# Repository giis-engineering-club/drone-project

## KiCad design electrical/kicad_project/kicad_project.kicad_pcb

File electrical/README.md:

# Electrical Engineering Subsystem (Flight Controller PCBA)

## Motivation
To design a highly robust, EMI-shielded 4-layer Power Distribution Network (PDN) and microcontroller logic board. This board must survive the extreme $di/dt$ inductive spikes generated by 40A ESC switching while providing mathematically clean SPI data to the ESP32 for 1000Hz PID loop execution.

## Architecture (Hierarchical Sheets)
We will use a Top-Down Hierarchical design in KiCad to keep the schematic industry-grade.
1. **`top_level.sch`**: The master block diagram connecting the sub-sheets.
2. **`power_distribution.sch`**: 5V to 3.3V LDO Regulator, LC filtering, and bulk/decoupling capacitors.
3. **`mcu_esp32.sch`**: The ESP32 logic, strapping pins, and UART/Programming headers.
4. **`sensors_imu.sch`**: The BMI270/MPU6000 IMU, SPI bus wiring, and strict decoupling.
5. **`io_connectors.sch`**: The ESC DSHOT pads, battery voltage sensing voltage-divider, and ESP-NOW RX pins.

## Critical Formulations
- **LC Filter Resonance (For IMU Power Cleanliness):** 
  $f_{res} = \frac{1}{2\pi \sqrt{L C}}$
  We must ensure $f_{res}$ is well below the 24kHz PWM frequency of the ESC to block high-frequency noise.
- **Trace Width Ampacity (IPC-2221):**
  $I = k \cdot \Delta T^b \cdot A^c$ 
  5V traces must handle 1A. Signal traces handle mere mA.
- **EMI Loop Area Minimization:**
  $V_{noise} = - \frac{d}{dt} \int \mathbf{B} \cdot d\mathbf{A}$
  Solid GND plane placed exactly 0.1mm below Layer 1 signal traces ensures $d\mathbf{A} \to 0$.

## Stack & Standards
- **EDA:** KiCad 8.0 (Apple Silicon Native)
- **Simulation:** NGSpice (Transient Power Analysis)
- **Manufacturing:** JLCPCB (4-Layer, 1oz Copper, SMT Assembly)

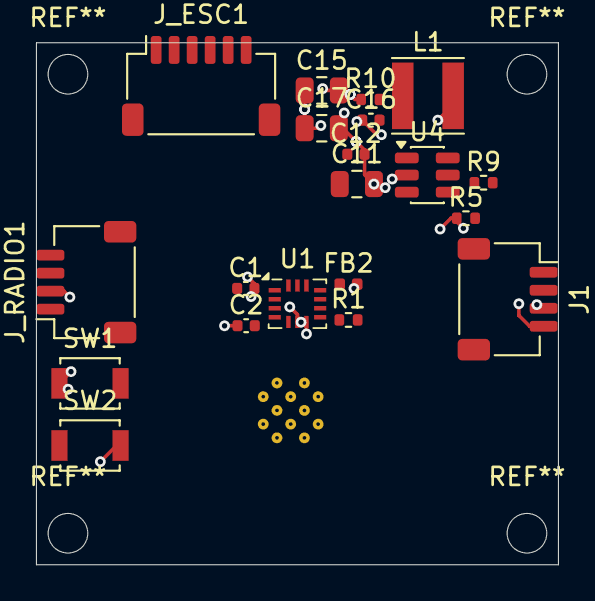
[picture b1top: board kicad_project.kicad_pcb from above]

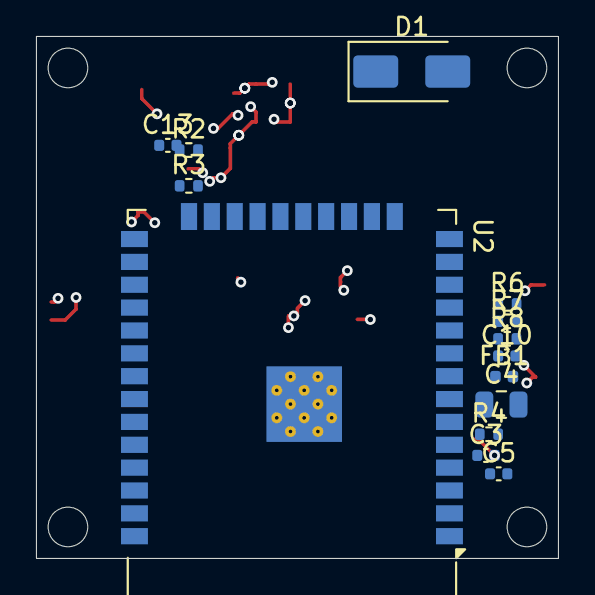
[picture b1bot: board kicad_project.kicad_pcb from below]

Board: 4 copper layers, 29.0 x 29.0 mm, 34 parts (14 on the bottom side), 27 nets.

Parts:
C1, C2, C5, C10: 100nF; C_0402_1005Metric
C3: 1µF; C_0402_1005Metric
C4: 22µF; C_0805_2012Metric
C11, C15, C17: 10uF; C_0805_2012Metric
C12, C13: 100nf; C_0402_1005Metric
C16: 1uF; C_0402_1005Metric
D1: SMAJ5.0A; D_SMA
FB1, FB2: FerriteBead; L_0402_1005Metric
J1: Conn_01x04; JST_SH_SM04B-SRSS-TB_1x04-1MP_P1.00mm_Horizontal
J_ESC1: Conn_01x06; JST_SH_SM06B-SRSS-TB_1x06-1MP_P1.00mm_Horizontal
J_RADIO1: Conn_01x04; JST_SH_SM04B-SRSS-TB_1x04-1MP_P1.00mm_Horizontal
L1: 2.2uH; L_Taiyo-Yuden_NR-40xx
R1, R3: 10k; R_0402_1005Metric
R2: 45.3k; R_0402_1005Metric
R4, R5: 10kΩ; R_0402_1005Metric
R6, R9: 100k; R_0402_1005Metric
R7: 22k; R_0402_1005Metric
R8: 1k; R_0402_1005Metric
R10: 0.22; R_0402_1005Metric
SW1, SW2: SW_Push; SW_SPST_B3U-1000P
U1: BMI160; Bosch_LGA-14_3x2.5mm_P0.5mm
U2: ESP32-WROOM-32
U4: SY8120B1ABC; SOT-23-6

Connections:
+3V3: C15.1, C16.1, C17.1, FB1.1, FB2.2, J1.3, L1.2, R2.1, R4.1, R5.1
+5V_DIRTY: C11.1, C12.1, D1.2 (A2), J_ESC1.1, J_RADIO1.1, R9.2, U4.5 (IN)
/IO connectors/DSHOT_M1: J_ESC1.3, U2.16 (IO13)
/IO connectors/DSHOT_M2: J_ESC1.4, U2.13 (IO14)
/IO connectors/DSHOT_M3: J_ESC1.5, U2.12 (IO27)
/IO connectors/DSHOT_M4: J_ESC1.6, U2.8 (IO32)
/IO connectors/UART_RX: J_RADIO1.4, U2.28 (IO17)
/IO connectors/UART_TX: J_RADIO1.3, U2.27 (IO16)
/MCU_ESP32/ESP32_ADC: C10.1, R8.2, U2.4 (SENSOR_VP)
/MCU_ESP32/IMU_CS: R1.2, U1.12 (CSB), U2.29 (IO5)
/MCU_ESP32/MISO: U1.1 (SDO), U2.31 (IO19)
/MCU_ESP32/MOSI: U1.14 (SDx), U2.37 (IO23)
/MCU_ESP32/SPI_SCK: U1.13 (SCx), U2.30 (IO18)
/sensors_imu/+3V3_IMU: C1.1, C2.2, FB2.1, R1.1, U1.5 (VDDIO), U1.8 (VDD)
GND: C1.2, C2.1, C3.2, C10.2, C11.2, C12.2, C15.2, C17.2, D1.1 (A1), J1.4, J_ESC1.2, J_RADIO1.2, R3.2, R7.1, R10.1, SW1.1, SW2.2, U1.6 (GNDIO), U1.7 (GND), U2.1 (GND), U2.15 (GND), U2.38 (GND), U2.39 (GND), U4.2 (GND)
unnamed: C4.1, C5.2, FB1.2
unnamed: C16.2, R10.2
unnamed: J1.1, U2.6 (IO34)
unnamed: J1.2, U2.7 (IO35)
unnamed: R6.1, R7.2, R8.1
unnamed: C3.1, R4.2, SW1.2, U2.3 (EN)
unnamed: R5.2, SW2.1, U2.25 (IO0)
unnamed: C4.2, C5.1, U2.2 (VDD)
unnamed: C13.1, U4.1 (BS)
unnamed: R9.1, U4.4 (EN)
unnamed: R2.2, R3.1, U4.3 (FB)
unnamed: C13.2, L1.1, U4.6 (LX)
